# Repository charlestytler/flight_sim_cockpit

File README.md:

# Flight Sim Cockpit

Repository for Hardware and Embedded Software for flight simulation cockpit and avionics panels that provide input/output for Flight Simulators (DCS).

The cockpit is modeled on a blend of F/A-18C, A-10C, F-15E, and F-16C cockpits.

## Software 

The software directory contains embedded software that runs on Arduino and Raspberry Pi microcontrollers.
These connect to a PC via USB and emulate USB HID joystick devices and also communicate with DCS-BIOS software.

To-do: Develop a Windows PC middleware to connect USB Serial -> Middleware -> DCS-BIOS and avoid flashing DCS module-specific code to the microcontrollers.

## Hardware

(Partially) assembled cockpit.  

### CAD Models

#### [Link to Fusion 360 Web Viewer of CAD Model](https://a360.co/4bIpcXp)
- Frame is built out of 2040 and 2020 aluminum extrusion according to the CAD model.
- Chair frame uses same extrusion and also 3D Printed TPU surrounding bearings for sliding in/out.
- For complex angles (such as left/right console outer rails and corners), extrusion connectors are 3D printed.
- The panels themselves are a mix of 3D prints or acrylic machined with a CNC router.
- Temporary labels are added with a Brother label maker and 6mm white on black tape.
- Permanent labels are made by painting white acrylic panels matte black and laser engraving the text and symbols.
- Glare shield is designed in multiple parts to enable printing on a 256x256 3D printer bed.

### PCBs

Current version of PCBs using:
 - Arduino Micro Pro (Atmel ATmega32U4)
    - Central processor for all I/O
    - Emulates a USB HID Joystick device
    - Communicates over Serial to PC middleware
    - Likely will upgrade to RP2040 Pico boards in next revision
 - PCF8575 I2C Expanders
    - Provides 16 digital I/O pins per board
    - Inputs used for Switches, Outputs used for indication LEDs
 - CD74HC4067 Multiplexers
    - Provides 16 to 1 analog input multiplexing
    - Used for reading analog potentiometers
 - RP2040 Raspberry Pi Pico (external of PCB)
    - Used for reading rotary encoders
    - Uses PIO to provide parallel handling of encoder interrupts
 - Screw Terminal breakouts

### Cockpit Layout

The layout of avionics panels is a combination of functions from multiple aircraft, so some panels are replicas of specific aircraft, where others are a mix of multiple or have labels renamed to more generic functionality.

#### [Link to Cockpit Layout comparison to Real Aircraft layouts [Figma document]](https://www.figma.com/design/4pN5J7COTx5o1YJxnx6NWO/Layout-Diagram?node-id=0-1&t=OCtYUoI0DKsqzIj2-1)

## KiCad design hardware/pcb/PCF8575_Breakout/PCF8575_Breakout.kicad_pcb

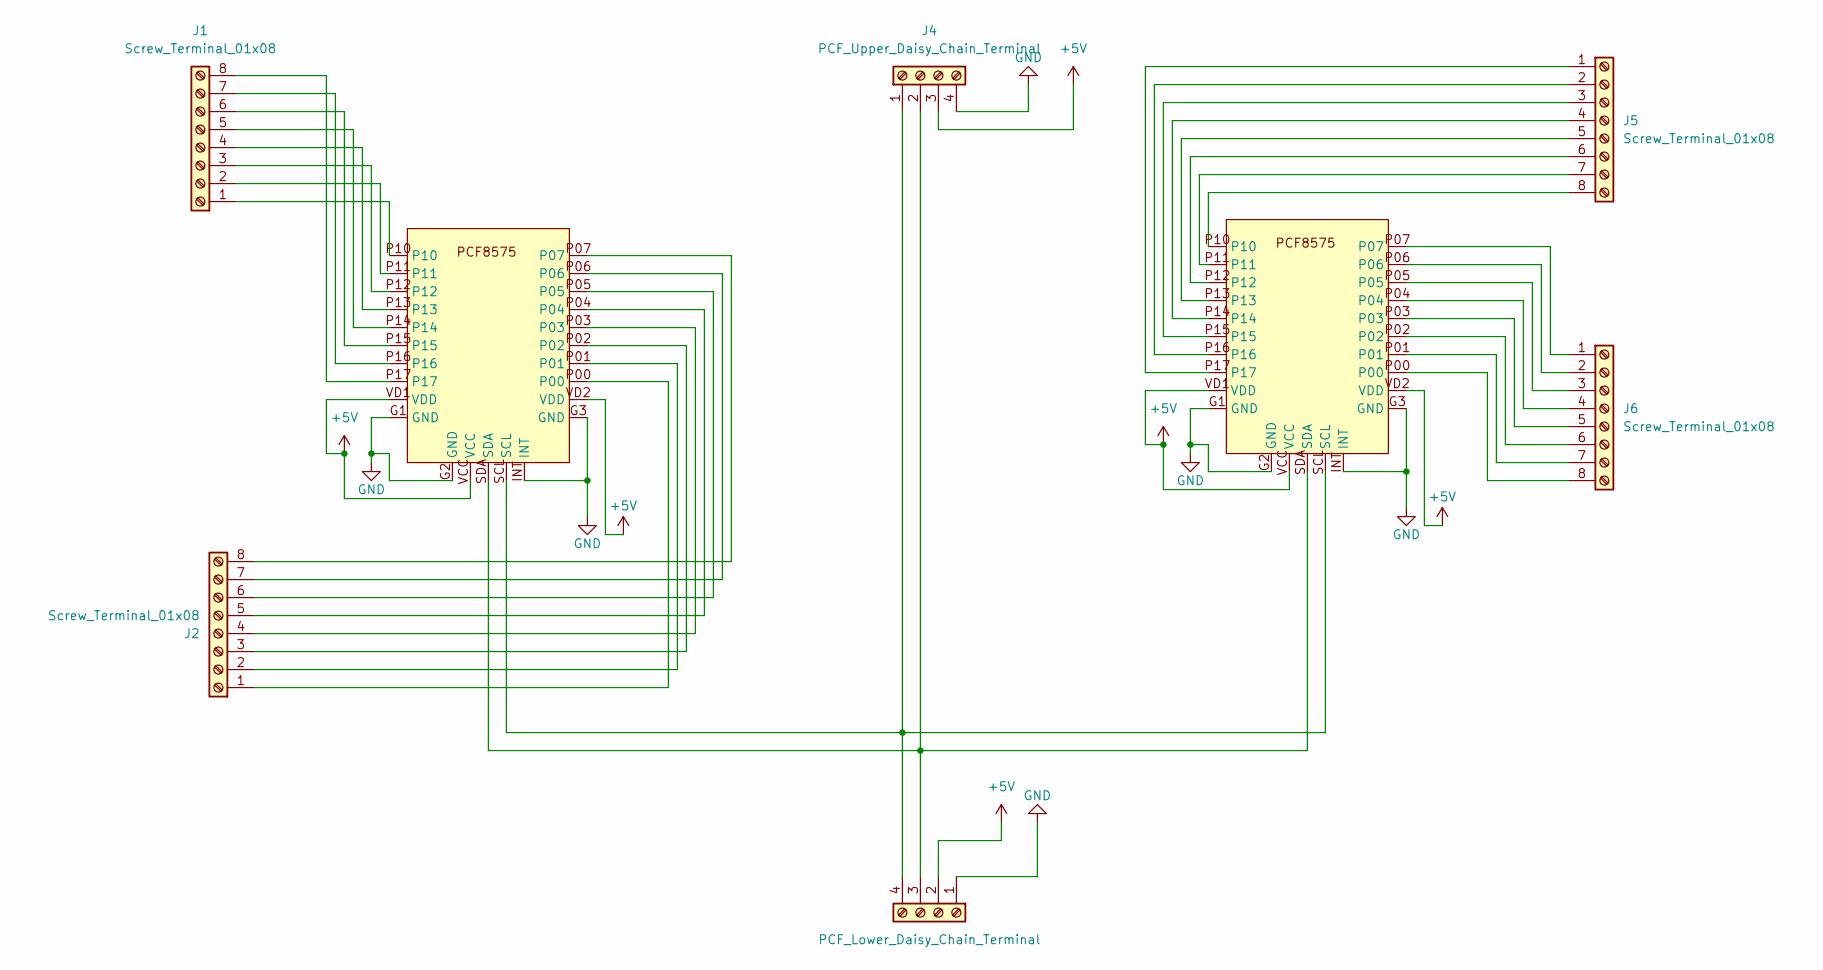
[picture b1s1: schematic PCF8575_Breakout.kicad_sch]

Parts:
J1, J2, J5, J6: Screw_Terminal_01x08; ScrewTerminal_2,5_8-G-5,08_1x08_P5.08mm_Vertical
J4: PCF_Upper_Daisy_Chain_Terminal; ScrewTerminal_2,5_4-G-5,08_1x04_P5.08mm_Vertical
J8: PCF_Lower_Daisy_Chain_Terminal; ScrewTerminal_2,5_4-G-5,08_1x04_P5.08mm_Vertical
U1, U3: PCF8575_Breakout

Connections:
+5V: J4.3, J8.2, U1.VCC, U1.VD1 (VDD), U1.VD2 (VDD), U3.VCC, U3.VD1 (VDD), U3.VD2 (VDD)
GND: J4.4, J8.1, U1.G1 (GND), U1.G2 (GND), U1.G3 (GND), U1.INT, U3.G1 (GND), U3.G2 (GND), U3.G3 (GND), U3.INT
unnamed: J1.1, U1.P10
unnamed: J1.2, U1.P11
unnamed: J1.3, U1.P12
unnamed: J1.4, U1.P13
unnamed: J1.5, U1.P14
unnamed: J1.6, U1.P15
unnamed: J1.7, U1.P16
unnamed: J1.8, U1.P17
unnamed: J2.1, U1.P00
unnamed: J2.2, U1.P01
unnamed: J2.3, U1.P02
unnamed: J2.4, U1.P03
unnamed: J2.5, U1.P04
unnamed: J2.6, U1.P05
unnamed: J2.7, U1.P06
unnamed: J2.8, U1.P07
unnamed: J4.1, J8.4, U1.SCL, U3.SCL
unnamed: J4.2, J8.3, U1.SDA, U3.SDA
unnamed: J5.1, U3.P17
unnamed: J5.2, U3.P16
unnamed: J5.3, U3.P15
unnamed: J5.4, U3.P14
unnamed: J5.5, U3.P13
unnamed: J5.6, U3.P12
unnamed: J5.7, U3.P11
unnamed: J5.8, U3.P10
unnamed: J6.1, U3.P07
unnamed: J6.2, U3.P06
unnamed: J6.3, U3.P05
unnamed: J6.4, U3.P04
unnamed: J6.5, U3.P03
unnamed: J6.6, U3.P02
unnamed: J6.7, U3.P01
unnamed: J6.8, U3.P00

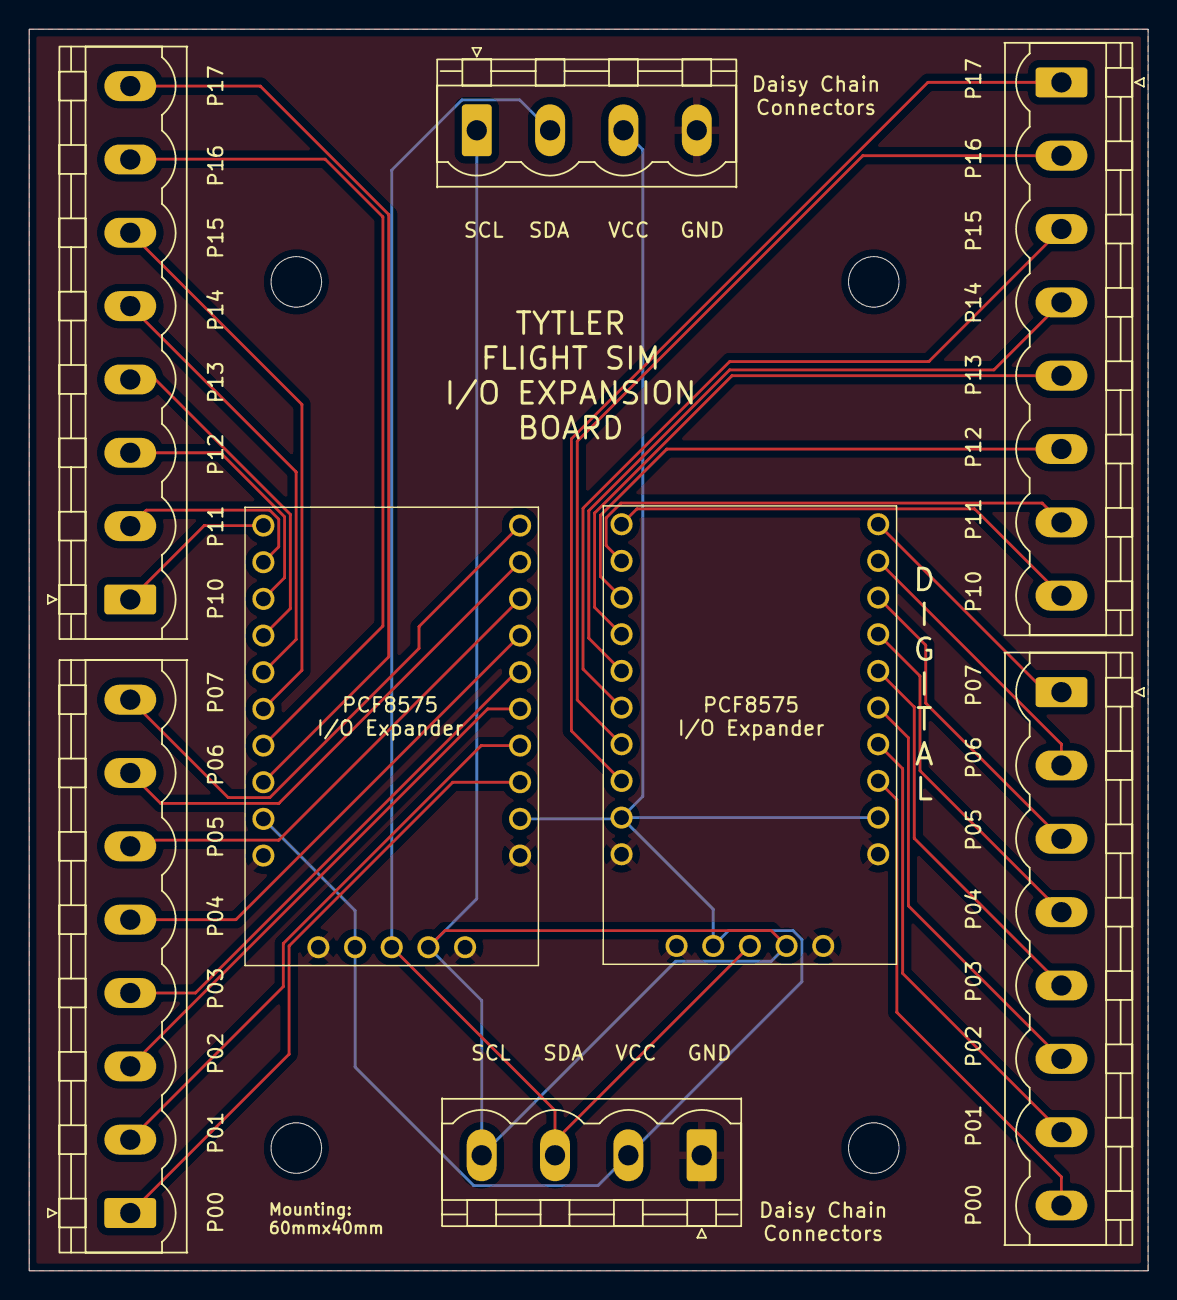
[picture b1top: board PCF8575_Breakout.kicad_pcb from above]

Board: 2 copper layers, 77.5 x 86.0 mm, 8 parts (0 on the bottom side), 36 nets.

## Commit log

2026-02-10 Update readme with PCB images
2026-02-10 Upload KiCAD PCB files
2026-02-10 Add CAD model image and link
2026-02-10 Move code into software/ directory with make instructions
